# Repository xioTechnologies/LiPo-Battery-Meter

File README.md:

LiPo-Battery-Meter
==================

Battery meter for single cell [LiPo batteries](https://www.sparkfun.com/products/339) to display a battery voltage between 2.8 V to 4.2 V as an LED bar graph.  Uses the [LM3914](https://www.sparkfun.com/products/12694).  The PCB has foot prints compatible with either ten 1206 LEDs or a [single LED bar graph package](https://www.sparkfun.com/products/9935).  Inspired by [Dave Jone's tutorial](http://www.eevblog.com/2011/09/29/eevblog-204-designing-a-li-ion-battery-gauge-with-the-lm3914/).

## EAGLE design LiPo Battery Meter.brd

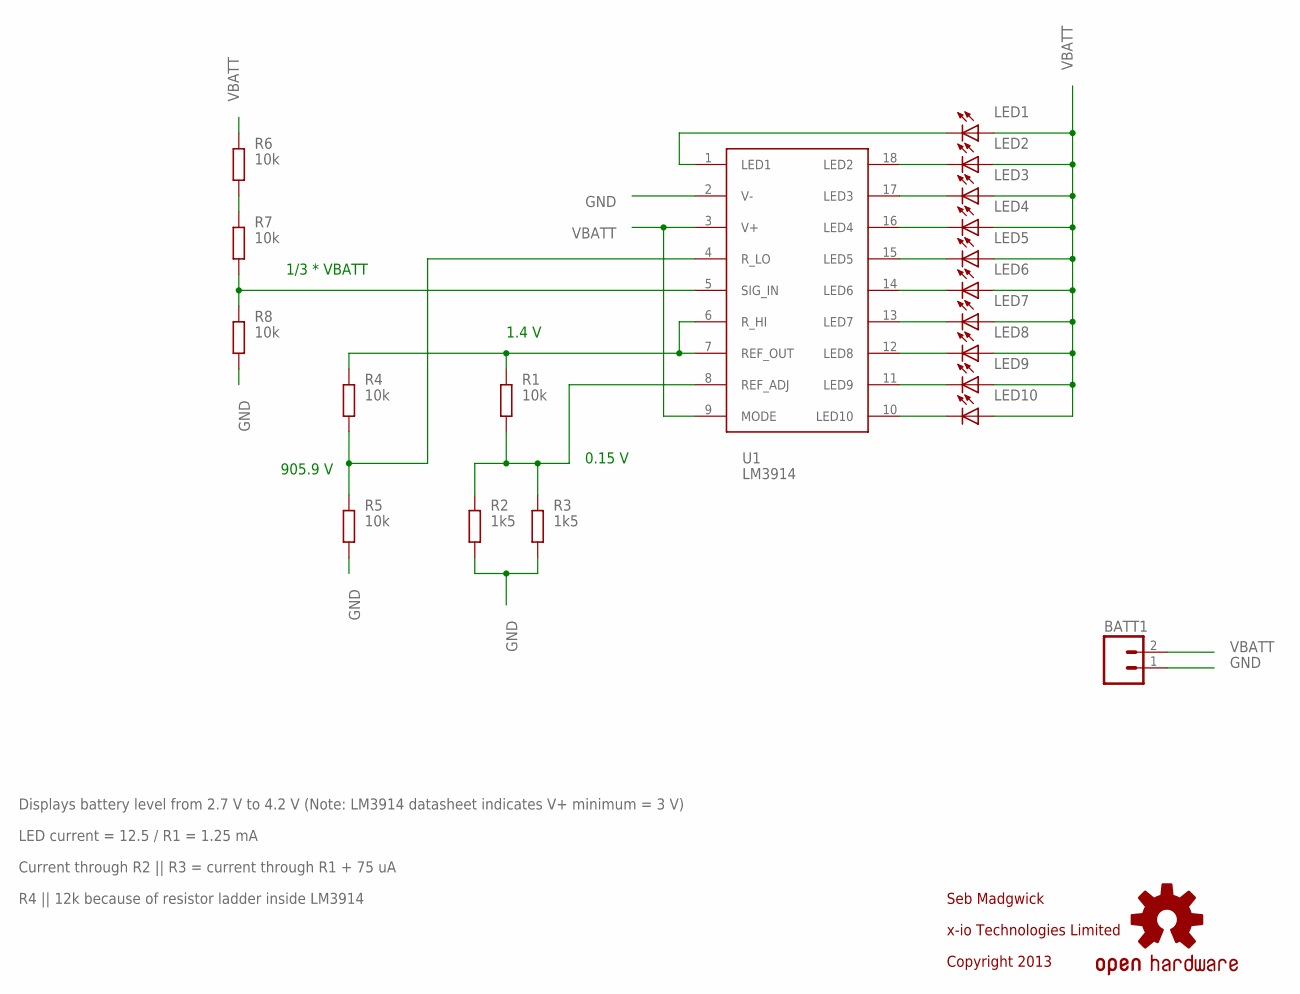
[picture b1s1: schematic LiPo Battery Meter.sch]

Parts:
BATT1: M02-JST-2MM-SMT; S2B-PH
LED1, LED2, LED3, LED4, LED5, LED6, LED7, LED8, LED9, LED10: LEDCHIPLED_1206; CHIPLED_1206
R1, R4, R5, R6, R7, R8: 10k; M1206
R2, R3: 1k5; M1206
U1: LM3914; DIL18
U$2: OSHW-LOGOM; OSHW-LOGO-M

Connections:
GND: BATT1.1, R2.1, R3.1, R5.1, R8.1, U1.2 (V-)
unnamed: R4.1, R5.2, U1.4 (R_LO)
unnamed: R7.1, R8.2, U1.5 (SIG_IN)
unnamed: R6.1, R7.2
unnamed: R1.1, R2.2, R3.2, U1.8 (REF_ADJ)
unnamed: LED10.C, U1.10 (LED10)
unnamed: LED9.C, U1.11 (LED9)
unnamed: LED8.C, U1.12 (LED8)
unnamed: LED7.C, U1.13 (LED7)
unnamed: LED6.C, U1.14 (LED6)
unnamed: LED5.C, U1.15 (LED5)
unnamed: LED4.C, U1.16 (LED4)
unnamed: LED3.C, U1.17 (LED3)
unnamed: LED2.C, U1.18 (LED2)
unnamed: LED1.C, U1.1 (LED1)
REF_OUT: R1.2, R4.2, U1.6 (R_HI), U1.7 (REF_OUT)
VBATT: BATT1.2, LED1.A, LED2.A, LED3.A, LED4.A, LED5.A, LED6.A, LED7.A, LED8.A, LED9.A, LED10.A, R6.2, U1.3 (V+), U1.9 (MODE)

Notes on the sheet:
Seb Madgwick
Copyright 2013
1.4 V
0.15 V
905.9 V
Displays battery level from 2.7 V to 4.2 V (Note: LM3914 datasheet indicates V+ minimum = 3 V)
1/3 * VBATT
Current through R2 || R3 = current through R1 + 75 uA
R4 || 12k because of resistor ladder inside LM3914
LED current = 12.5 / R1 = 1.25 mA
x-io Technologies Limited

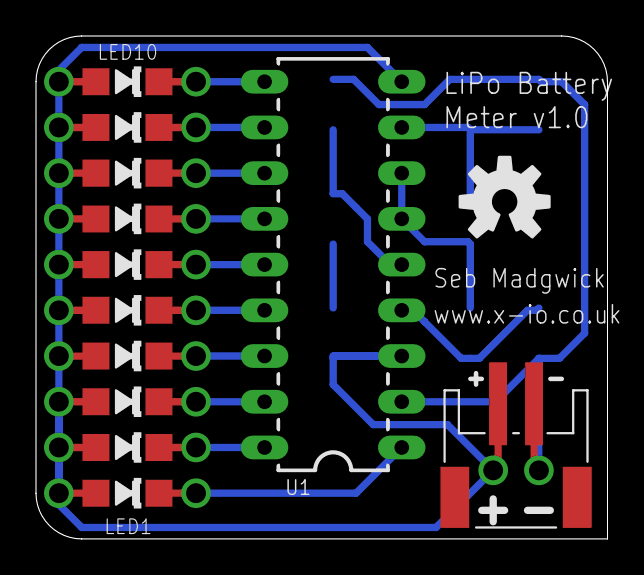
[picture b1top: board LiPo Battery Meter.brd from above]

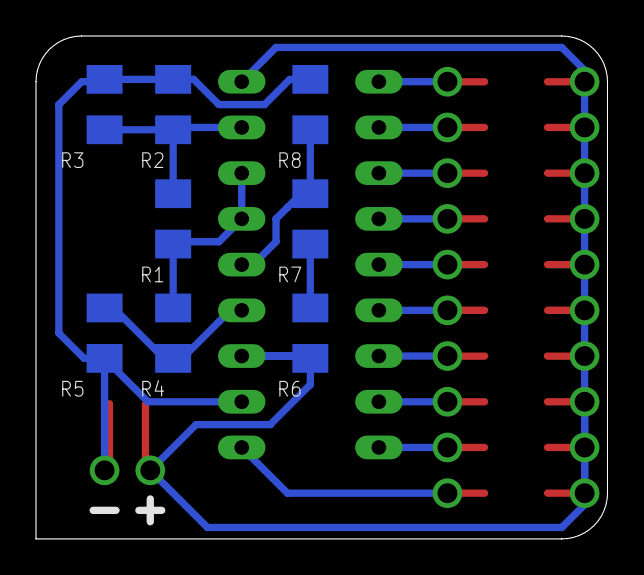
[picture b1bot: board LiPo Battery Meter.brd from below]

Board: 2 copper layers, 31.8 x 27.9 mm, 23 parts (8 on the bottom side), 17 nets.

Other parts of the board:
U$1: LIPO_BATTERY_METER_V1_0_BOTTOM
U$3: LIPO_BATTERY_METER_V1_0_TOP

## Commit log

2014-04-13 Add project files
2014-04-13 Correct files names
2014-04-13 Update image
2014-04-21 Change silkscreen to 500 DPI

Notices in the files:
parts and their libraries:
SparkFun: Licensing: CC v3.0 Share-Alike You are welcome to use this library for commercial purposes.
